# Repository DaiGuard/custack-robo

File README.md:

# ｶｽﾀｯｸﾛﾎﾞ (Custack-robo)

custack-robo のゲーム演出およびロボット連携を行うための統合リポジトリです。
Jetson 上での画像認識・位置推定、ホストPC/Unity 上でのプロジェクション演出・共有メモリ連携、M5Stack/ATtiny による実機制御を行います。

---

## 📁 フォルダ構成

```text
jetson/ (ワークスペースルート)
├── README.md
├── aiplan/            # システム設計・実装計画書
├── custack_ws/        # ROS 2 (Humble) ワークスペース
│   ├── build_jetson.sh    # Jetson 用クリーン＆ビルドスクリプト (locator + web)
│   ├── build_host.sh      # ホスト用クリーン＆ビルドスクリプト (router)
│   ├── run_locator.sh     # カメラ認識・自己位置推定ノード起動スクリプト
│   ├── run_router.sh      # 共有メモリ・シリアルルーターノード起動スクリプト
│   ├── run_web.sh         # キャリブレーション用 Web UI サーバー起動スクリプト
│   └── src/               # ROS 2 パッケージ群 (custack_locator_cpp, custack_router, custack_web, custack_msgs)
├── custack-unity/     # Unity プロジェクト (ゲーム演出・共有メモリ高速連携)
│   └── Assets/Scenes/MultiDisplayProjects/Scripts/
│       ├── SharedMemoryPoseViewer.cs  # 共有メモリ 3台位置姿勢インスペクターモニター
│       ├── SharedMemoryManager.cs     # 共有メモリ送受信・コントローラ連携マネージャー
│       └── RosManager.cs              # ROS-TCP 連携マネージャー (レガシー)
├── custack-robot/     # 実機ロボット制御ファームウェア
│   ├── robot_main/        # M5Stack Core2 メイン統括プログラム
│   ├── robot_bridge/      # M5Atom Matrix ESP-NOW ブリッジプログラム
│   ├── robot_arm/         # ATtiny1614 アーム制御プログラム
│   └── robot_leg/         # ATtiny1614 脚・オムニホイール制御プログラム
└── custack-hardware/  # ハードウェア CAD・回路設計データ
```

---

## 🚀 クイックスタート

### 1. Jetson 環境 (位置推定・カメラ認識)
```bash
# ワークスペースディレクトリへ移動
cd custack_ws

# クリーン＆ビルド
./build_jetson.sh

# 位置推定ノード起動
./run_locator.sh
```

### 2. ホストPC環境 (ルーターノード & Unity)
```bash
# ワークスペースディレクトリへ移動
cd custack_ws

# クリーン＆ビルド
./build_host.sh

# ルーターノード起動 (共有メモリ & M5Atom シリアル中継)
./run_router.sh
```
Unity 側で `custack-unity` プロジェクトを開き、`SharedMemoryPoseViewer` または `SharedMemoryManager` を利用してゲームを実行します。

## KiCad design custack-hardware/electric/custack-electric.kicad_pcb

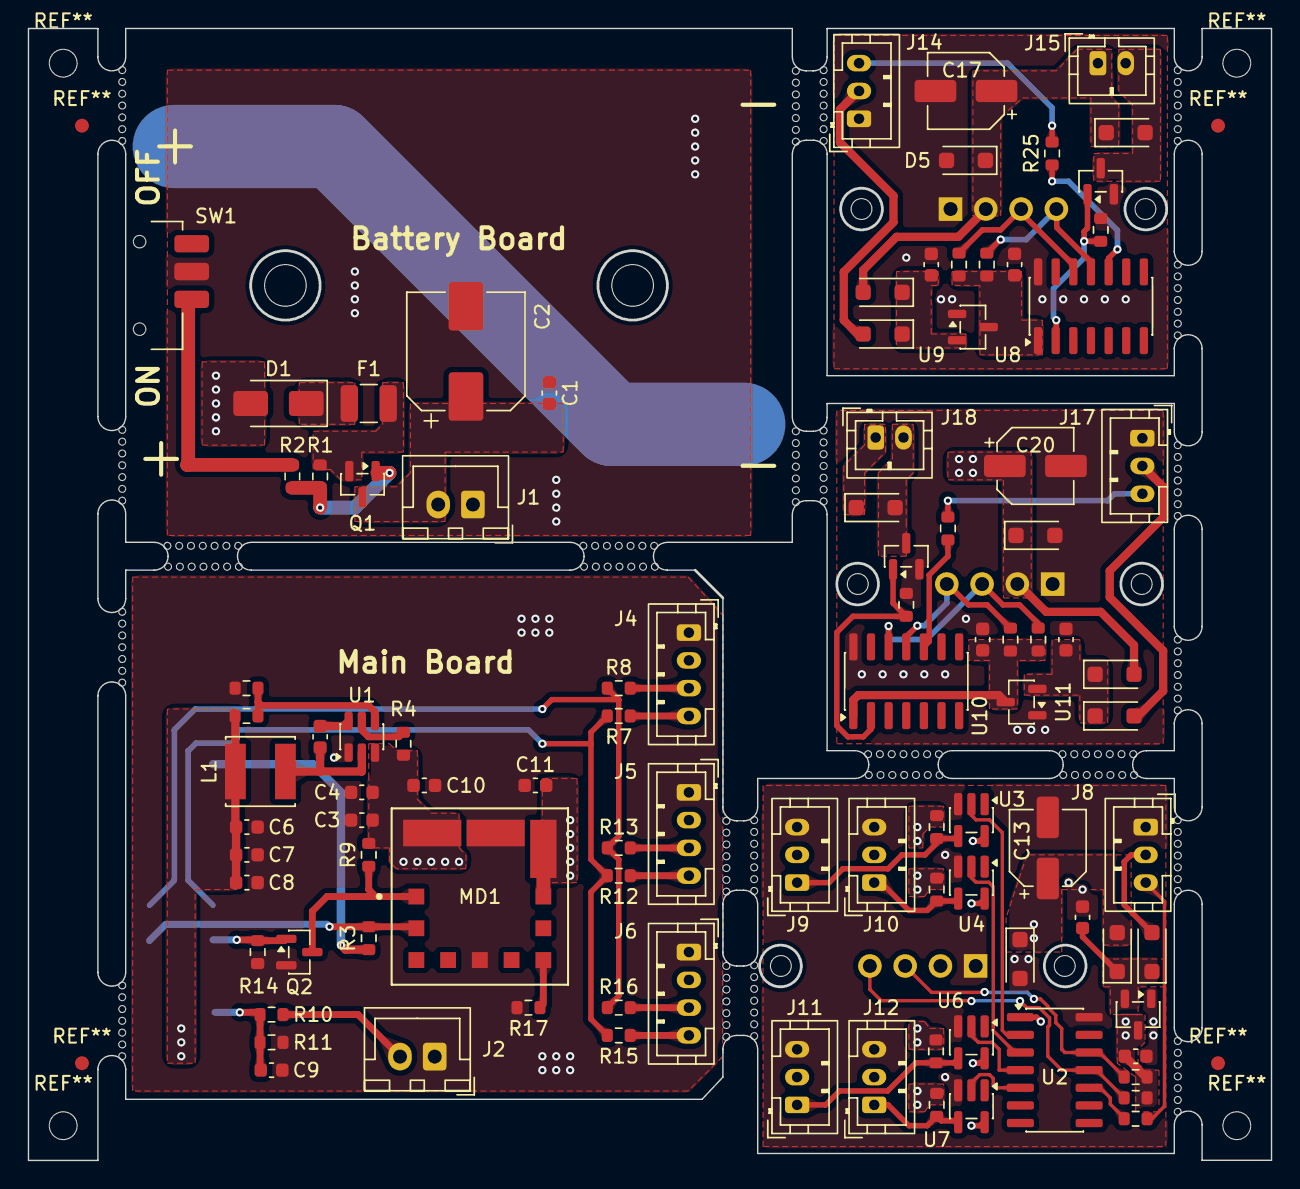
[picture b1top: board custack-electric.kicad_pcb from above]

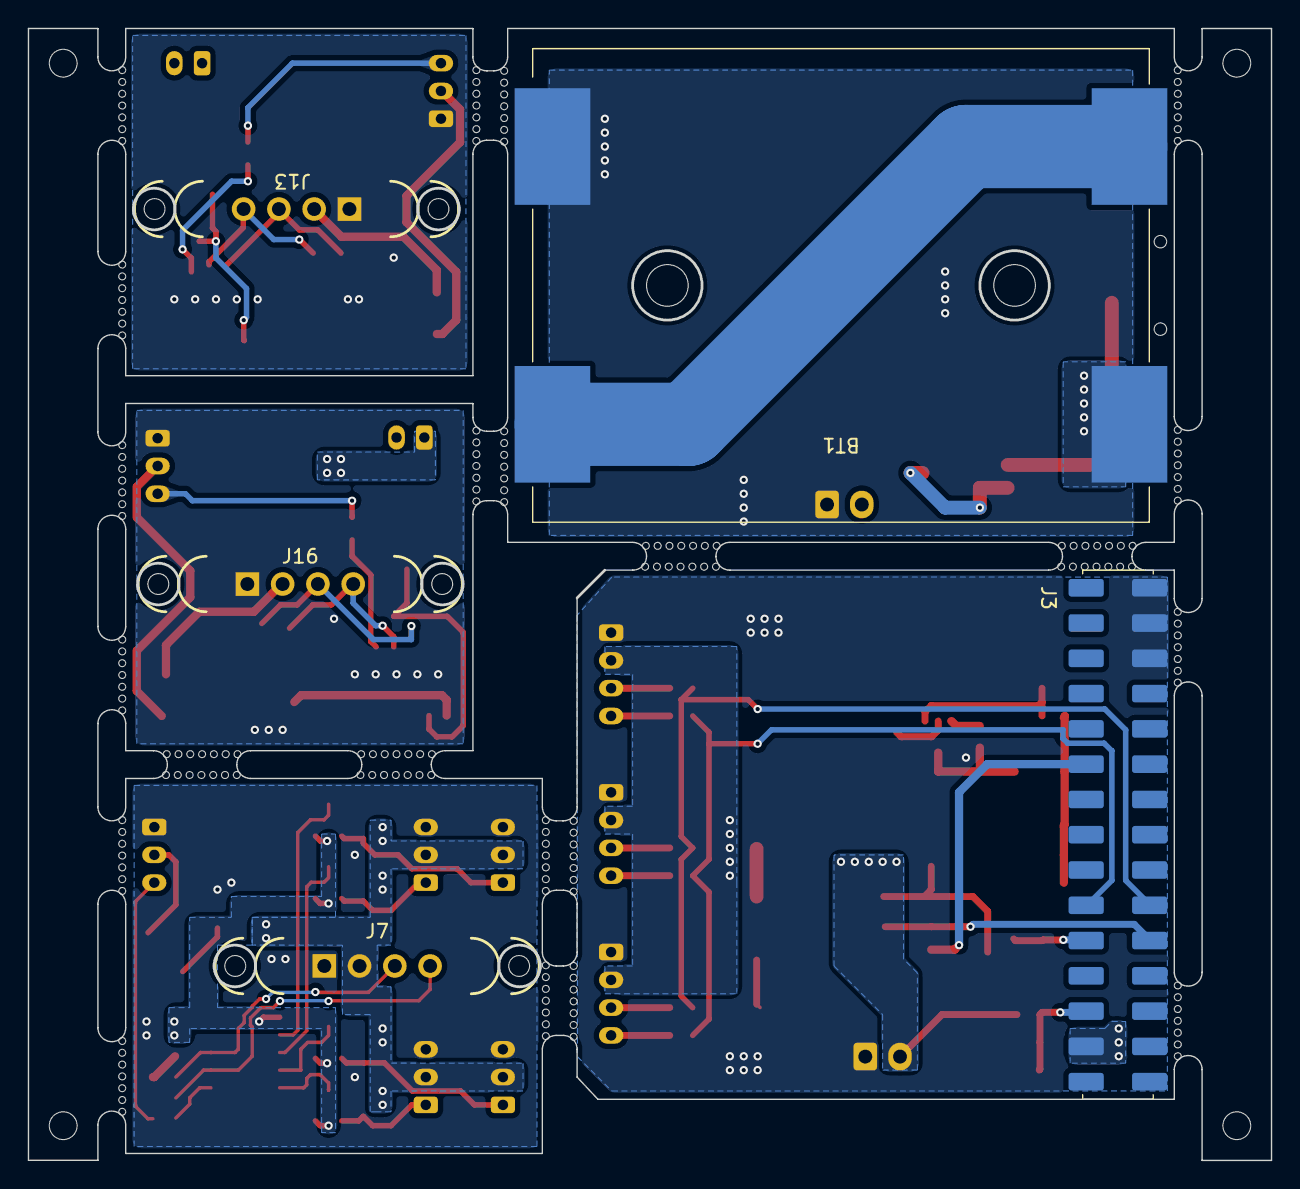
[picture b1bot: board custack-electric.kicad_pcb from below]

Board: 2 copper layers, 89.5 x 81.5 mm, 102 parts (5 on the bottom side), 69 nets.

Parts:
BT1: 18350 2S; 18350_2S_custom
C1: 10µF 25V X5R; C_0603_1608Metric
C2: 220µF 25V 105°C; CP_Elec_8x10
C3, C4, C10, C11, C14, C15, C18, C19, C22, C23: 10µF 25V X5R 0603; C_0603_1608Metric
C5, C9: 0.1µF 25V X8R 0603; C_0603_1608Metric
C6, C7, C8: 22µF 10V X5R 0603; C_0603_1608Metric
C13, C17, C20: 100µF 16V 105°C; CP_Elec_5x5.9
D1: 20V 3A Vf=500mV; D_SMA
D2, D5, D9: 7V 16.7A; D_SOD-123F
D3, D4, D6, D7, D8, D10, D11, D12: Vr:30V, 2A Vf:430mV; D_SOD-123F
F1: 12V 6A 5s 1210; Fuse_1210_3225Metric
J1: XH 2.5mmピッチ 2極 オス AWG22; JST_XH_B2B-XH-A_1x02_P2.50mm_Vertical
J2: XH 2.5mmピッチ 2極 オス AWG24; JST_XH_B2B-XH-A_1x02_P2.50mm_Vertical
J3: 2x15P@2.54mm SMD; M5Stack_Bus_Socket
J4, J5, J6: PH 2mmピッチ 4極 オス AWG24; JST_PH_B4B-PH-K_1x04_P2.00mm_Vertical
J7, J13, J16: 4P MMale magnetic connector (Earhole); Pogopin_1x4_2.54mm
J8, J9, J10, J11, J12, J14, J17: PH 2mmピッチ 3極 オス AWG24; JST_PH_B3B-PH-K_1x03_P2.00mm_Vertical
J15, J18: PH 2mmピッチ 2極 オス AWG24; JST_PH_B2B-PH-K_1x02_P2.00mm_Vertical
L1: 3.3µH 4.2A 35.1mohm; IND_VLS5045EX-3R3N
MD1: IN:4.5V-14V,OUT:0.591V-5.5V,6A; MURATA_OKL-T-6-W12N-C_0
Q1: MOSFET P-CH 20V 6A SOT23F; SOT-23
Q2, Q3, Q4: N-ch 30V 4A SOT23F; SOT-23
R1, R2, R3, R4, R9, R14, R19, R20, R26, R27, R28, R30, R31, R32: 10K 1/4W ±5% 0603; R_0603_1608Metric
R5: 54.9K 1/10W ±1% 0603; R_0603_1608Metric
R6, R10: 10K 1/10W ±1% 0603; R_0603_1608Metric
R7, R8, R12, R13, R15, R16: 0ohm 1/10W 0603; R_0603_1608Metric
R11: 5.1K 1/10W ±1% 0603; R_0603_1608Metric
R17: 1.2K 1/10W ±1%; R_0603_1608Metric
R18, R25, R29: 330ohm 1/3W ±5% 0603; R_0603_1608Metric
R21, R22, R23, R24: 4.7kohm 1/4W ±5% 0603; R_0603_1608Metric
SW1: 12V 100mA; SW_SPDT_CSS121
U1: IN:4.5V-17V, OUT:0.765V-7V,2A; TSOT-23-6
U2, U8, U10: 20MHz 16KB FLASH; SOIC-14_3.9x8.7mm_P1.27mm
U3, U4, U6, U7: 非反転 1.65-5.5V, 32mA SOT-23-5; SC-74A-5_1.55x2.9mm_P0.95mm
U5, U9, U11: Vin(MAX): 13.2V, Vout: 3.3V 250mA; SOT-23-3

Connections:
/battery_board/+BATT: F1.2, Q1.2 (S), R1.1
/battery_board/+VSW: C1.2, C2.1, J1.2, Q1.3 (D)
/battery_board/GND: BT1.4 (-), C1.1, C2.2, J1.1, SW1.2 (B)
/leftarmunit_board/+3.3V: C23.1, R30.2, R31.2, U10.1 (VDD), U11.3 (VO)
/leftarmunit_board/EXT_SCA: J16.3, R30.1, U10.12 (PA2)
/leftarmunit_board/EXT_SCL: J16.4, R31.1, U10.11 (PA1)
/leftarmunit_board/GND: C20.2, C22.2, C23.2, D9.2 (A), J16.1, J17.1, Q4.2 (S), R32.1, U10.14 (GND), U11.1 (GND)
/leftarmunit_board/PWM1: Q4.1 (G), R32.2, U10.2 (PA4)
/leftarmunit_board/UPDI: R29.2, U10.10 (PA0/RESET/UPDI)
/leftarmunit_board/VBUS: D10.2 (A), J17.2
/leftarmunit_board/VDD: C20.1, D9.1 (K), D11.2 (A), D12.1 (K), J16.2, J18.1
/legunit_board/+3.3V: C15.1, R19.2, R20.2, U2.1 (VDD), U3.5 (VCC), U4.5 (VCC), U5.3 (VO), U6.5 (VCC), U7.5 (VCC)
/legunit_board/EXT_SCA: J7.3, R19.1, U2.12 (PA2)
/legunit_board/EXT_SCL: J7.4, R20.1, U2.11 (PA1)
/legunit_board/GND: C13.2, C14.2, C15.2, D2.2 (A), J7.1, J8.1, J9.3, J10.3, J11.3, J12.3, U2.14 (GND), U3.3 (GND), U4.3 (GND), U5.1 (GND), U6.3 (GND), U7.3 (GND)
/legunit_board/PWM1: U2.2 (PA4), U3.2 (A)
/legunit_board/PWM2: U2.3 (PA5), U4.2 (A)
/legunit_board/PWM3: U2.4 (PA6), U6.2 (A)
/legunit_board/PWM4: U2.5 (PA7), U7.2 (A)
/legunit_board/UPDI: R18.2, U2.10 (PA0/RESET/UPDI)
/legunit_board/VBUS: D3.2 (A), J8.2
/legunit_board/VDD: C13.1, D2.1 (K), D4.2 (A), J7.2, J9.2, J10.2, J11.2, J12.2, R21.2, R22.2, R23.2, R24.2
/main_board/+3.3V: J3.21, R3.2
/main_board/+5V: C6.1, C7.1, C8.1, J3.29, L1.2, R5.1
/main_board/+VSW: C3.1, C4.1, C10.1, J2.2, MD1.2 (VIN), R4.1, R9.1, R10.2, U1.3 (VIN)
/main_board/BATSEN: C9.1, J3.28, R10.1, R11.2
/main_board/EXT_SCA: J3.10, R8.2, R13.2, R16.2
/main_board/EXT_SCL: J3.25, R7.2, R12.2, R15.2
/main_board/GND: C3.2, C4.2, C6.2, C7.2, C8.2, C9.2, C10.2, C11.2, J2.1, J3.1, J3.2, J3.3, J4.1, J5.1, J6.1, MD1.3 (1_GROUND), MD1.7 (2_GROUND), Q2.2 (S), R6.2, R11.1, R14.1, R17.1, U1.1 (GND)
/main_board/GOOD: J3.11, MD1.10 (POWER_GOOD_OUT), R3.1
/main_board/ON/OFF: J3.26, Q2.1 (G), R14.2
/main_board/ON/OFF_CTRL: MD1.1 (~ON/OFF_CONTROL), Q2.3 (D), R9.2
/main_board/VDD: C11.1, J4.2, J5.2, J6.2, MD1.4 (VOUT), MD1.5 (SENSE)
/rightarmunit_board/+3.3V: C19.1, R26.2, R27.2, U8.1 (VDD), U9.3 (VO)
/rightarmunit_board/EXT_SCA: J13.3, R26.1, U8.12 (PA2)
/rightarmunit_board/EXT_SCL: J13.4, R27.1, U8.11 (PA1)
/rightarmunit_board/GND: C17.2, C18.2, C19.2, D5.2 (A), J13.1, J14.1, Q3.2 (S), R28.1, U8.14 (GND), U9.1 (GND)
/rightarmunit_board/PWM1: Q3.1 (G), R28.2, U8.2 (PA4)
/rightarmunit_board/UPDI: R25.2, U8.10 (PA0/RESET/UPDI)
/rightarmunit_board/VBUS: D6.2 (A), J14.2
/rightarmunit_board/VDD: C17.1, D5.1 (K), D7.2 (A), D8.1 (K), J13.2, J15.1
unnamed: BT1.2 (-), BT1.3 (+)
unnamed: BT1.1 (+), D1.2 (A)
unnamed: D1.1 (K), F1.1
unnamed: C14.1, D3.1 (K), D4.1 (K), U5.2 (VI)
unnamed: C18.1, D6.1 (K), D7.1 (K), U9.2 (VI)
unnamed: D8.2 (A), J15.2, Q3.3 (D)
unnamed: C22.1, D10.1 (K), D11.1 (K), U11.2 (VI)
unnamed: D12.2 (A), J18.2, Q4.3 (D)
unnamed: J4.3, R8.1
unnamed: J4.4, R7.1
unnamed: J5.3, R13.1
unnamed: J5.4, R12.1
unnamed: J6.3, R16.1
unnamed: J6.4, R15.1
unnamed: J8.3, R18.1
unnamed: J9.1, R21.1, U3.4 (Y)
unnamed: J10.1, R22.1, U4.4 (Y)
unnamed: J11.1, R23.1, U6.4 (Y)
unnamed: J12.1, R24.1, U7.4 (Y)
unnamed: J14.3, R25.1
unnamed: J17.3, R29.1
unnamed: MD1.6 (TRIM), R17.2
unnamed: Q1.1 (G), R1.2, R2.1
unnamed: R2.2, SW1.3 (C)
unnamed: R4.2, U1.5 (EN)
unnamed: C5.2, L1.1, U1.2 (SW)
unnamed: C5.1, U1.6 (VBST)
unnamed: R5.2, R6.1, U1.4 (VFB)

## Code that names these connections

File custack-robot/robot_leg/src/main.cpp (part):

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// -----------------------------------------------------------------------------
// ハードウェア・ピン定義 (ATtiny1614)
// -----------------------------------------------------------------------------
#define PIN_PWM1   PIN_PA4
#define PIN_PWM2   PIN_PA5
#define PIN_PWM3   PIN_PA6
#define PIN_PWM4   PIN_PA7

// -----------------------------------------------------------------------------
// 各車輪の回転方向係数 (+1: 通常, -1: 反転)
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// -----------------------------------------------------------------------------
// サーボインスタンス
// -----------------------------------------------------------------------------
static Servo servo1; // PWM1 (PA4)
static Servo servo2; // PWM2 (PA5)
static Servo servo3; // PWM3 (PA6)
static Servo servo4; // PWM4 (PA7)

// -----------------------------------------------------------------------------
// 定数設定
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    pulse4 = clamp_val(pulse4, (uint16_t)SERVO_MIN_US, (uint16_t)SERVO_MAX_US);

    // PWM信号出力（停止時もニュートラルパルスを出力し続ける）
    servo1.writeMicroseconds(pulse1); // PWM1 (PA4): 右後
    servo2.writeMicroseconds(pulse2); // PWM2 (PA5): 右前
    servo3.writeMicroseconds(pulse3); // PWM3 (PA6): 左後
    servo4.writeMicroseconds(pulse4); // PWM4 (PA7): 左前

#elif DEVICE_ID == 0x02
    //----------------------------------------------------------------------
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
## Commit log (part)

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2025-05-03 20250503作業
2025-05-03 20250503作業_2
2025-05-03 20250503作業_3
2025-05-03 20250503作業_4
2025-05-03 20250503作業_5
2025-05-03 20250503作業_6
2025-05-03 20250503作業_7
2025-05-03 20250503作業_8
2025-05-04 20250504作業
2025-05-05 20250505作業
2025-05-05 20250505作業_2
2025-05-06 20250506作業
2025-05-07 20250507作業
2025-05-07 依存関係ファイルを追加
2025-05-07 20250507作業_2
2025-05-10 20250510作業
2025-05-10 20250510作業_2
2025-05-11 20250511作業
2025-05-11 20250511作業_2
2025-05-11 20250511作業_3
2025-05-11 unityプロジェクトの追加
2025-05-11 20250511作業_4
2025-05-21 マルチプレイヤー機能の追加
2025-05-23 ros2モジュール追加
2025-05-25 Unityが開けなくなった
2025-05-25 Ros2パッケージ追加
2025-05-29 レーザーエフェクト作成
2025-06-15 2プレイヤーに特定のコントローラ割当テスト
2025-06-17 マルチコントローラのシリアルNo確認処理追加
2025-06-18 マルチプレーヤの追加と削除機能追加
2025-06-19 武器調整中
2025-06-20 Squashed commit of the following:
    commit 7b0316c1343a4dc5051742795300257c068fdaeb
    Author: DaiGuard <zenith.or.w@gmail.com>
    Date: Fri Jun 20 09:04:43 2025 +0900
    add weapon
2025-06-20 ミサイル処理の変更
2025-06-20 不要パッケージの削除
2025-06-20 ゲームバージョン作成
2025-06-21 README追加
2025-06-21 README修正
2025-06-21 トップ画像の作成
2025-06-21 ZeroMQ通信作成中
2025-06-21 Squashed commit of the following:
    commit 754b384a1d19ccbed725060f320a1cb3866352cb
    Author: DaiGuard <zenith.or.w@gmail.com>
    Date: Sat Jun 21 20:32:55 2025 +0900
    トップ画像の作成
2025-06-22 ZeroMQクラスの作成
2025-06-22 ゲーム試作中
2025-06-24 マーカ位置サーバーの作成中
2025-06-28 ホモグラフィ計算の追加
2025-06-29 ZeroMQ送信機能の追加
2025-06-29 ZeroMQ送信機能のバグ修正
2025-06-29 ZeroMQ Unityとの通信をテスト
2025-06-29 Unityへの転送をテスト完了
2025-06-29 実際の投影テスト
2025-06-30 フィールド試作
2025-06-30 ロボットレンダリングを試作
2025-06-30 シャットダウンボタンの追加
2025-07-02 README.mdの修正
2025-07-02 コントローラ接続を実装
2025-07-02 コントローラ通信を実装
2025-07-02 README.md の更新
2025-07-06 だいたい実装完了
2025-07-06 REAME.mdの追加
2025-09-28 ROBO_WCOMのホスト、ロボット機能を追加
2025-09-28 コントローラ操作用サーバーの追加
2025-09-29 add controller birdige, host, robot project
2025-09-29 3player support
2025-09-29 weapon control fix
2025-09-30 controller for dual wheel type
2025-10-01 add 4 wheel drive control
2025-10-07 use inmft2025
2025-10-07 unity security patch
2025-10-07 READMEの追記
2026-01-05 add markerpos_pub package
2026-01-05 add marker pose publisher
2026-01-10 2026/01/10 15:54 v1.0.2 ソースコード削除
    フォルダ構成とプログラムのバージョン管理方法を変更するため
    一度、中身をすべて削除します
2026-01-10 2026/01/10 15:59 フォルダ初期状態を作成
    作業を開始するに当たり、フォルダの初期状態を作成
    ここからは各ブランチで作業を継続実施する
2026-01-10 2026/01/10 22:00 マーカ位置サーバーの作成
    Jetson上でROSノードとして実行する
    ROS humbleで起動するためホストPCもhumbleを
    要求すること
2026-01-10 2026/01/10 ros-tcp-endpointの追加
    Unityが直接ROSメッセージを受け取ることができないので
    Jetson側でros-tcp-endpointを実行するよう変更
    それに伴いlaunch起動と停止をできるように起動・停止スクリプトを変更
2026-01-11 2026/01/11 13:52 ROS通信テストシーン作成
    ROS通信を行うためのテストシーンを作成
2026-01-16 2026/01/17 02:27 Unity+ROS対応
    カメラサーバーだけROS対応に変更
2026-01-16 2026/01/17 02:28 新Unityプロジェクト作成中
    ROSシステムに入れ替えたプロジェクトを作成中
2026-01-18 2026/01/18 22:12 KMMF参加適合
    KMMFに参加した内容で現場適合させたもの
2026-01-18 2026/01/18 22:15 KMMF現場適合
    KMMF参加時の現場適合作業
2026-05-04 初期アップロード
2026-05-04 カメラユニット内ROSパッケージをアップロード
    - custack_locator_cpp
    - custack_msgs
    - custack_web
    依存する他パッケージをsubmoduleに追加
    - vision_opencv
    - ROS-TCP-Endpoint
2026-05-04 add .gitignore for ROS workspace
2026-05-04 AIレビューに向けたファイルを追加
2026-05-05 ros_tcp_endpointと通信するため/robot_posesのQoSを変更 best_effort -> reliable レイテンシを後で確認する
2026-05-05 this commit is adding custack-unity.
2026-05-05 change homography matrix file
2026-05-05 Unity側のROSインスタンス登録タイミングを変更
2026-05-05 change package RosTcpConnector low latency original repository
2026-05-05 custack_locator_cpp low latency modify
2026-05-05 Remove submodule: ROS-TCP-Endpoint
2026-05-05 original ROS-TCP-Endpoint
2026-05-05 Remove submodule
2026-05-05 ROS-TCP-Endpointの最速設定テスト
2026-05-05 ROS-TCP-Connectorの最新アップデート
2026-05-05 リポジトリ変更
2026-05-05 サブモジュールアップデート
2026-05-06 UpdateメソッドをFixedUpdateからLateUpdateに変更
2026-05-17 電子回路作業用のフォルダを作成
2026-05-17 電子回路フォルダ用の整理
2026-05-18 電子回路で使用しているシンボルをジェネリックシンボルに入れ替え
2026-05-24 電子回路設計が一旦完成
2026-05-25 型番確定作業途中
2026-05-31 electric circut complete
2026-06-07 electric circuit complete
2026-06-07 pcb board complete
